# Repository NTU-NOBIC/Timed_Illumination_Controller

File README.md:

# Timed Illumination Controller

Firmware for an **Arduino Teensy 4.0** that coordinates two LED-control outputs with camera acquisition. In timed acquisition, the Teensy generates an external camera trigger and monitors the camera's trigger-ready feedback. A second mode uses camera feedback to control LED illumination during externally controlled continuous streaming.

## Features

- **Timed acquisition:** programmable camera trigger intervals (`t1`–`t4`) and LED lead/lag intervals (`t5`–`t8`).
- **Streaming mode:** LED control based on the camera feedback input and configurable `ts` interval.
- **Two active-HIGH channels:** Channel A and Channel B, with firmware-enforced mutual exclusion.
- **Camera monitoring:** frame-event counting from the camera feedback signal (mode-dependent validation).
- **Serial interface:** status, timing, acquisition, streaming, manual LED control, and configuration commands at **115200 baud**.
- **EEPROM presets:** save/load timing, cycle count, and selected channel in slots **0–10**; slot **0** is read at startup.

## Firmware and connections

Main sketch: [`Timed_Cam_Trig_LED_Control.ino`](Timed_Cam_Trig_LED_Control.ino)

| Teensy 4.0 pin | Firmware name | Direction | Purpose |
|---|---|---|---|
| 9 | `CAM_TRIG_OUT` | Output | Active-HIGH camera external trigger |
| 10 | `CAM_TRIG_READY` | Input (`INPUT_PULLUP`) | Camera feedback |
| 13 (`LED_BUILTIN`) | `GATE_A` | Output | Active-HIGH Channel A gate (also onboard LED) |
| 14 | `GATE_B` | Output | Active-HIGH Channel B gate |

**Important:** Confirm interface voltage levels, signal polarity, camera feedback configuration, and external LED driver requirements before connecting hardware. The sketch's naming of its camera and signals does not establish compatibility with every camera configuration.
Note: Teensy 4.0 GPIO input and output logic voltage is 3.3V.

## Quick start

1. Open `Timed_Cam_Trig_LED_Control.ino` in an Arduino environment configured for **Teensy 4.0**.
2. Compile and upload the sketch to the board.
3. Open a serial terminal at **115200 baud** and send commands terminated by a newline.
4. Send `help` to display the implemented commands or `?` to view status and timing settings.
5. For timed acquisition, configure the camera for the expected external-trigger/ready-signal operation, then issue `r`. Enter `q` followed by Enter to abort the timed run.
6. For streaming mode, ensure the camera feedback input is configured for the exposure signal expected by the firmware, then issue `stm on`; use `stm off` to disable the mode.

See [**USER_GUIDE.md**](./firmware/USER_GUIDE.md) under firmware folder for full commands, parameter definitions, default values, operating procedures, and EEPROM details.

## Documentation scope

This README describes functionality present in the supplied `.ino` sketch. Channel names A/B are firmware labels; the sketch does **not** assign LED colours or fluorescence filter bands. Camera operation and image saving must be verified separately on the actual system.

## Disclaimer and licensing

The firmware is provided without any assurance of suitability or safe operation with a particular hardware configuration. Review and test signal timing and electrical interfaces before use.

**License:** No license grant has been inferred from the `.ino` source. Add an appropriate `LICENSE` file only after confirming the intended licensing terms with the code's rights holders.

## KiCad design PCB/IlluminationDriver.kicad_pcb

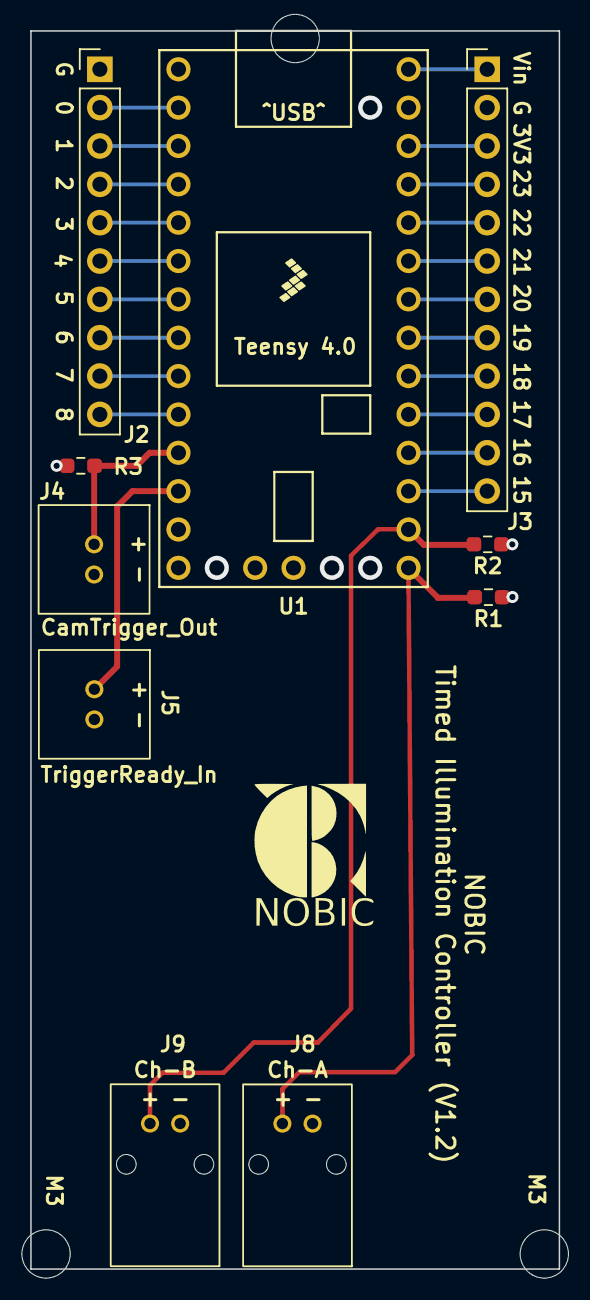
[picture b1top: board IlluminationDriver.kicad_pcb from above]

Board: 2 copper layers, 35.0 x 82.0 mm, 13 parts (0 on the bottom side), 25 nets.

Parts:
H1, H2, H3: MountingHole; MountingHole_3.2mm_M3_DIN965
J2: 801-87-010-10-001101; PinHeader_1x10_P2.54mm_Vertical
J3: 801-87-012-10-001101; PinHeader_1x12_P2.54mm_Vertical
J4, J5: DF51K-2P-2DSA(800); DF51K-2P-2DSA
J8, J9: DF51KB-2P-2DS(800); DF51K-2P-2DS
R1, R2: 10k; R_0603_1608Metric_Pad0.98x0.95mm_HandSolder
R3: 100k; R_0603_1608Metric_Pad0.98x0.95mm_HandSolder
U1: DEV-15583 (Sparkfun Teensy 4.0); Teensy4p0_NoSMTs_Redux

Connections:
/CamTrigger_Out: J4.2, R3.2, U1.11 (9_OUT1C)
/GATE_A: J8.1, R1.2, U1.20 (13_SCK_CRX1_LED)
/GATE_B: J9.1, R2.2, U1.21 (14_A0_TX3_SPDIF_OUT)
/TriggerReady_In: J5.2, U1.12 (10_CS_MQSR)
GND: J2.1, J3.2, J4.1, J5.1, J8.2, J9.2, R1.1, R2.1, R3.1, U1.1 (GND), U1.17 (GND), U1.32 (GND)
unnamed: J2.2, U1.2 (0_RX1_CRX2_CS1)
unnamed: J2.3, U1.3 (1_TX1_CTX2_MISO1)
unnamed: J2.4, U1.4 (2_OUT2)
unnamed: J2.5, U1.5 (3_LRCLK2)
unnamed: J2.6, U1.6 (4_BCLK2)
unnamed: J2.7, U1.7 (5_IN2)
unnamed: J2.8, U1.8 (6_OUT1D)
unnamed: J2.9, U1.9 (7_RX2_OUT1A)
unnamed: J2.10, U1.10 (8_TX2_IN1)
unnamed: J3.1, U1.33 (VIN)
unnamed: J3.3, U1.31 (3V3)
unnamed: J3.4, U1.30 (23_A9_CRX1_MCLK1)
unnamed: J3.5, U1.29 (22_A8_CTX1)
unnamed: J3.6, U1.28 (21_A7_RX5_BCLK1)
unnamed: J3.7, U1.27 (20_A6_TX5_LRCLK1)
unnamed: J3.8, U1.26 (19_A5_SCL0)
unnamed: J3.9, U1.25 (18_A4_SDA0)
unnamed: J3.10, U1.24 (17_A3_TX4_SDA1)
unnamed: J3.11, U1.23 (16_A2_RX4_SCL1)
unnamed: J3.12, U1.22 (15_A1_RX3_SPDIF_IN)
